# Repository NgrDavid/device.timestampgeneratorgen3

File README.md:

## Harp Timestamp Generator Gen3

This device generates programable timestamps to up to 6 harp devices.

### Key Features ###

* TBA

### Connectivity ###

* TBA

## Interface ##

The interface with the Harp Output Expander can be done through [Bonsai](https://bonsai-rx.org/).

## Licensing ##

Each subdirectory will contain a license or, possibly, a set of licenses if it involves both hardware and software.

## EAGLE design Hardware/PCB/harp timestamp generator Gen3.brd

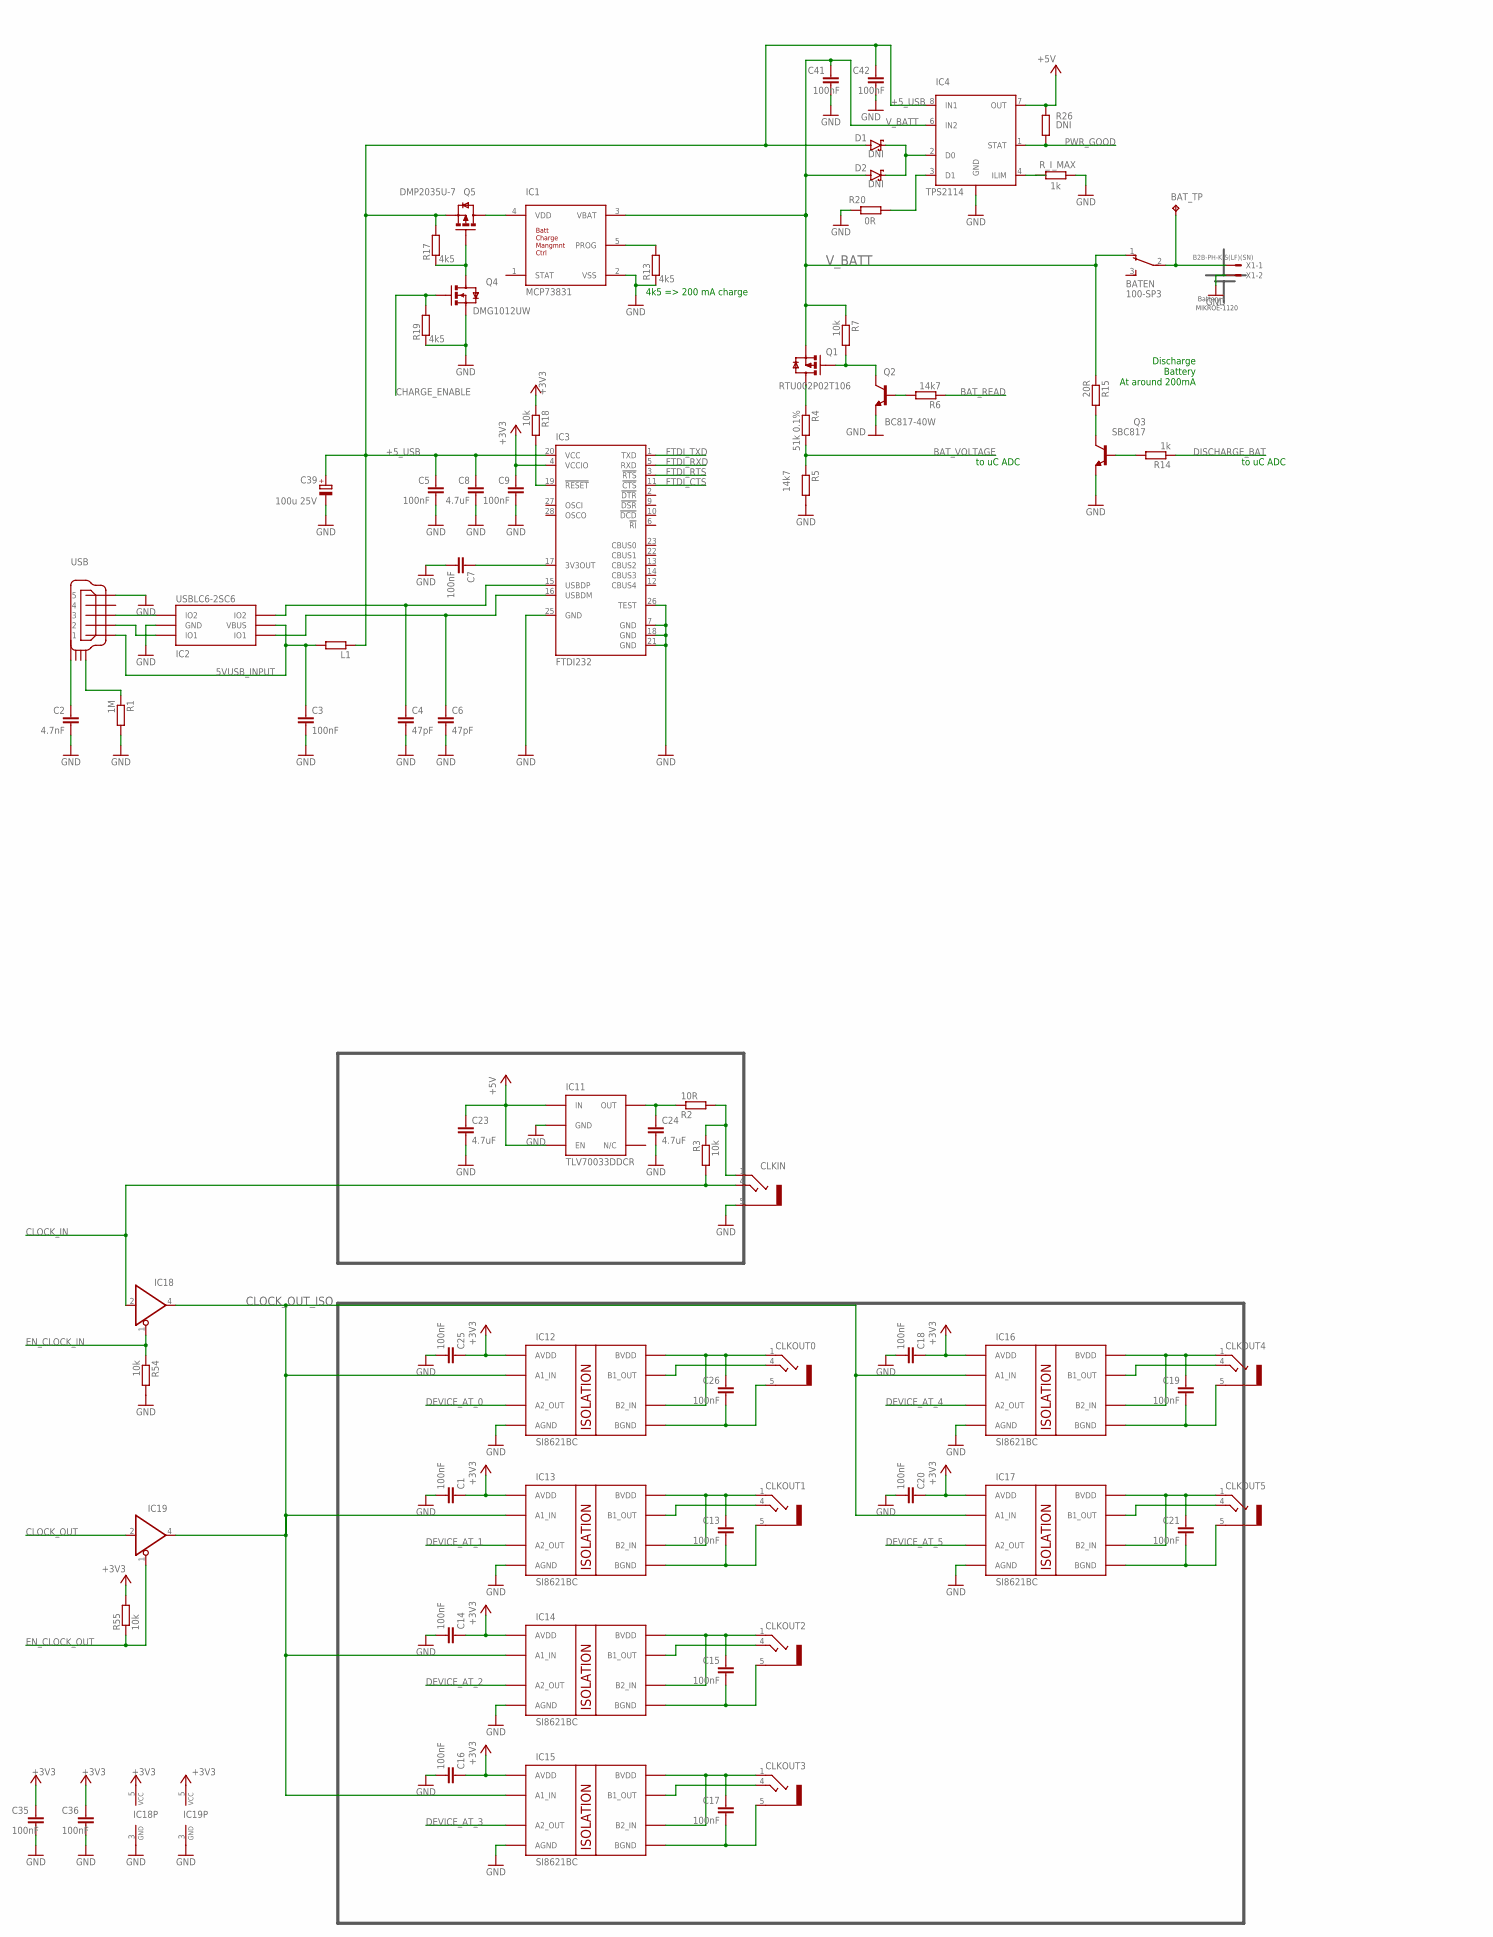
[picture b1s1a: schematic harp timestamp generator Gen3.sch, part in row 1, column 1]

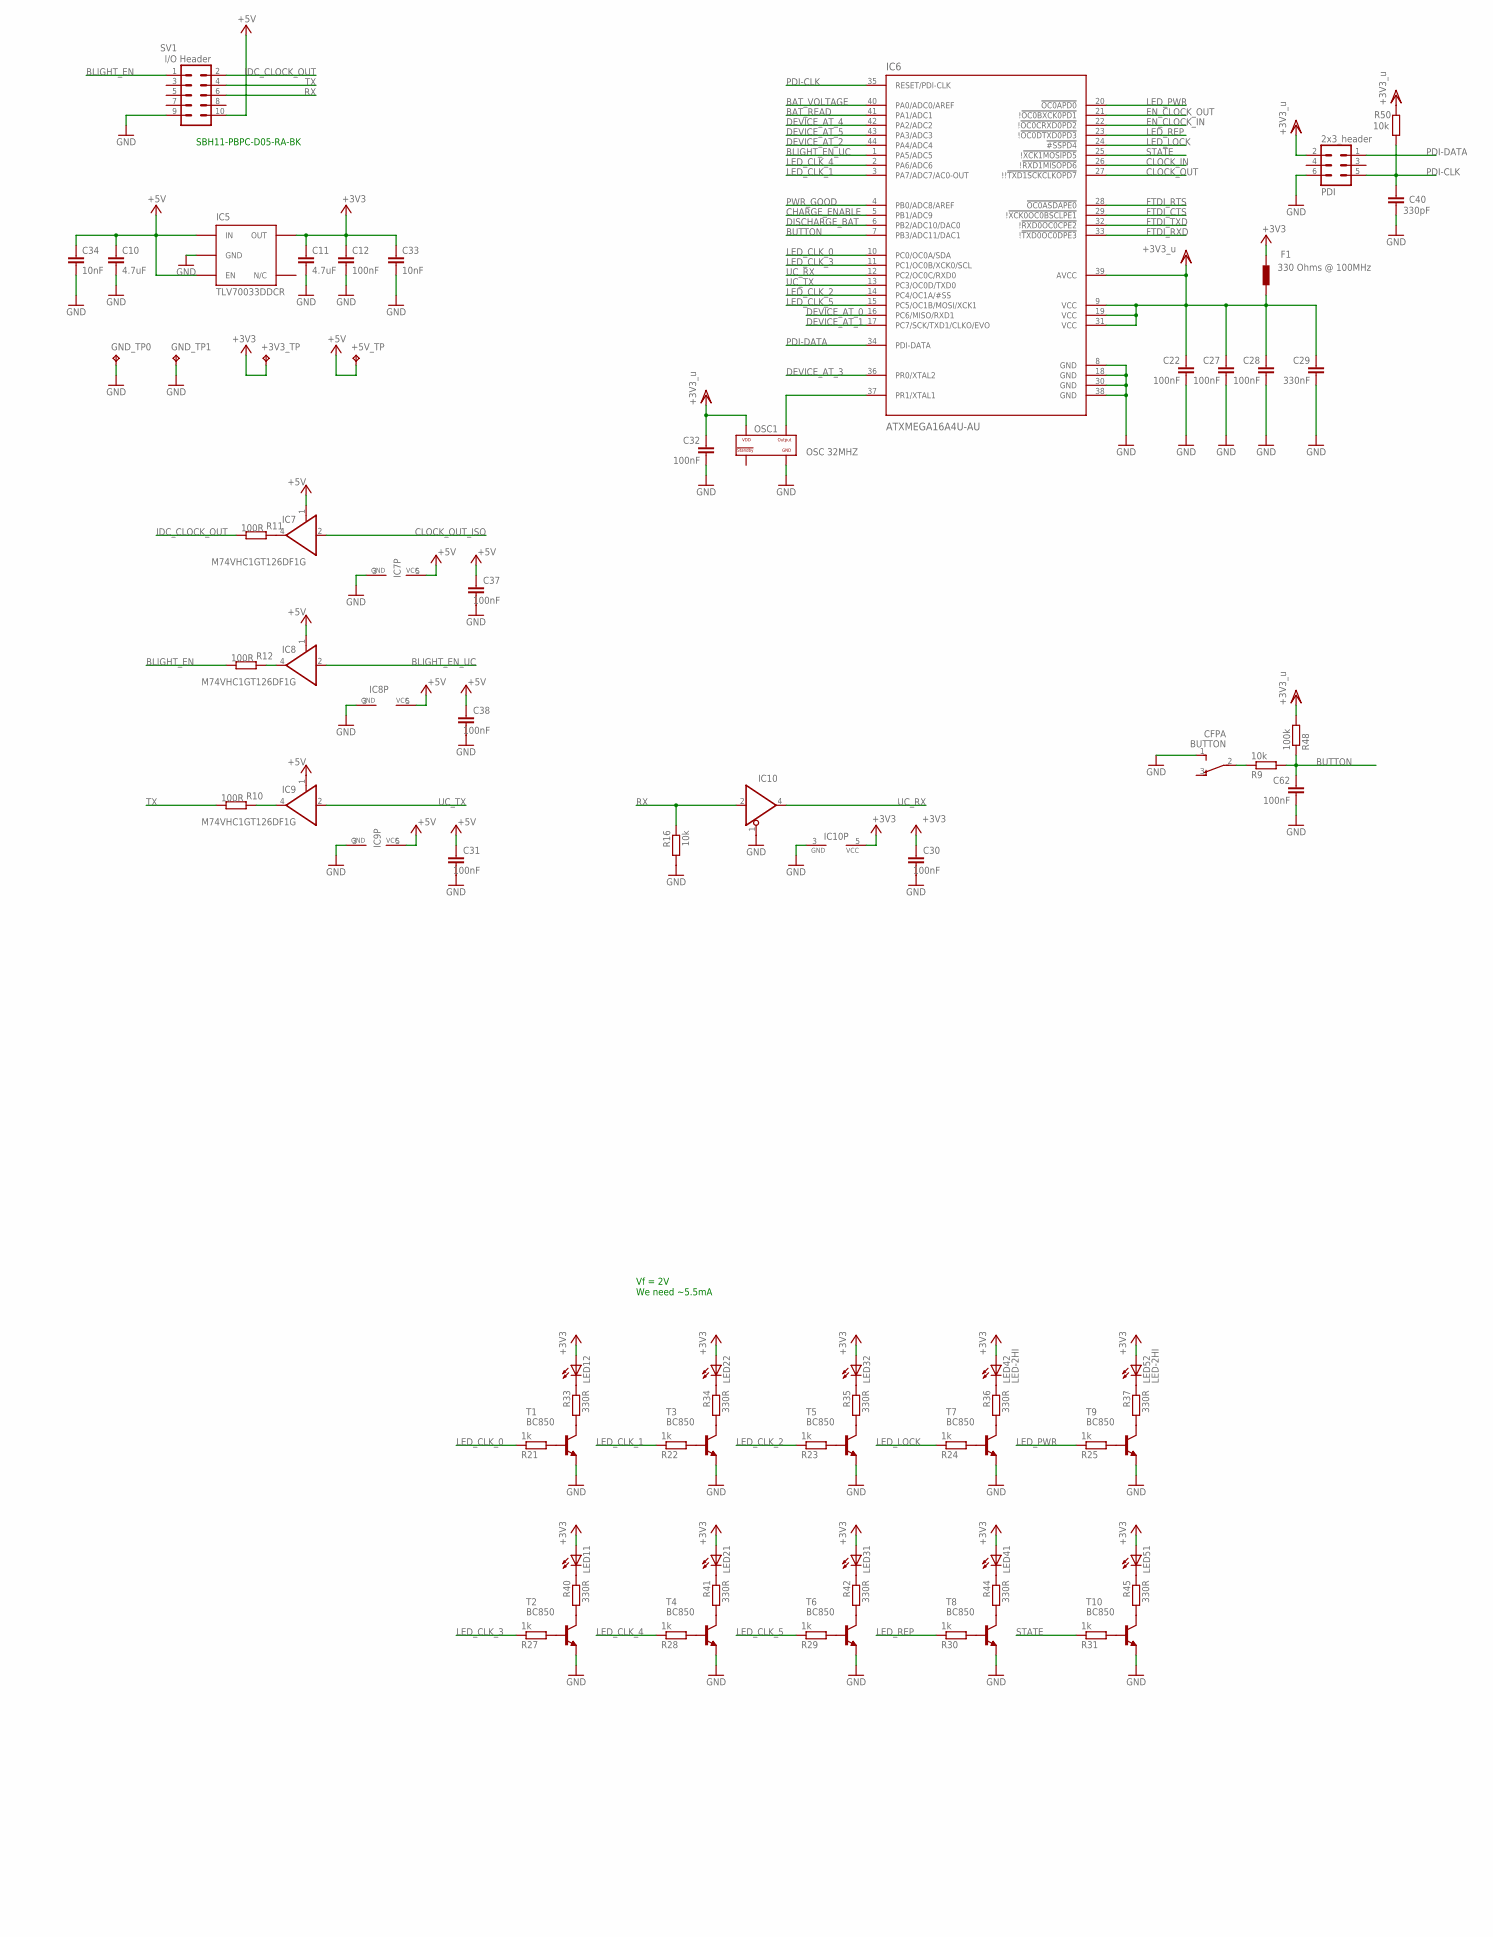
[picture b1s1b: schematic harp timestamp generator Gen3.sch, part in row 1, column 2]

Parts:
+3V3_TP, +5V_TP: TPPAD1-13; P1-13; MPN n.a.
BATEN: 100-SP3; 2M1-SP1-T2-B4-M6RE; MPN 7101MD9ABE; DIGIKEY_PN CKN1045-ND Mouser: 611-7101-051
BAT_TP: TPPAD1-13; P1-13; MPN n.a.
BUTTON: CFPA; MPN CFPA-1FB4-A2T; DIGIKEY_PN 563-1246-1-ND
C1, C3, C5, C7, C9, C12, C13, C14, C15, C16, C17, C18, C19, C20, C21, C22, C25, C26, C27, C28, C30, C31, C32, C35, C36, C37, C38, C41, C42, C62: 100nF; C0402; MPN CGA2B3X7R1H104K050BB; DIGIKEY_PN 445-6899-2-ND
C2: 4.7nF; C0402; MPN UMK105B7472KV-F; DIGIKEY_PN 587-2237-1-ND
C4, C6: 47pF; C0402; MPN 04025A470JAT2A; DIGIKEY_PN 478-1078-1-ND
C8, C10, C11, C23, C24: 4.7uF; C0603; MPN EMK107ABJ475KA-T; DIGIKEY_PN 587-2786-1-ND
C29: 330nF; C0402; MPN GRM155R61A334KE15D; DIGIKEY_PN 490-3263-1-ND
C33, C34: 10nF; C0402; MPN CL05B103KB5NNNC; DIGIKEY_PN 1276-1028-1-ND
C39: 100u 25V; TT2D6; MPN EEUFM1E101B; DIGIKEY_PN P19702CT-ND
C40: 330pF; C0402; MPN C0402C331JAGAC7867; DIGIKEY_PN 399-11875-1-ND
CLKIN: CLCK_JACK; 35RASMT2BHNTRX; MPN 35RASMT2BHNTRX; DIGIKEY_PN SC1489-1-ND
CLKOUT0, CLKOUT1, CLKOUT2, CLKOUT3, CLKOUT4, CLKOUT5: CLCK_JACK; 35RASMT2BHNTRX; MPN 35RASMT2BHNTRX; DIGIKEY_PN SC1489-1-ND
D1, D2: DNI; SOD3715X135
F1: 330 Ohms @ 100MHz; R0603; MPN BLM18SG331TN1D; DIGIKEY_PN 490-3997-1-ND
GND_TP0, GND_TP1: TPPAD1-13; P1-13; MPN n.a.
IC1: MCP73831; TSOT23-5; DIGIKEY_PN MCP73831T-2ATI/OTCT-ND
IC2: USBLC6-2SC6; SOT23-6L; MPN USBLC6-2SC6; DIGIKEY_PN 497-5235-1-ND
IC3: FTDI232; SSOP28; MPN FT232RL-REEL; DIGIKEY_PN 768-1007-1-ND
IC4: TPS2114; TSSOP8; MPN TPS2114APWR; DIGIKEY_PN 296-16939-1-ND
IC5, IC11: TLV70033DDCR; TSOT23-5; MPN TLV70033DDCR; DIGIKEY_PN 296-27937-6-ND
IC6: ATXMEGA16A4U-AU; QFP80P1200X1200X120-44N; MPN ATXMEGA16A4U-AU; DIGIKEY_PN ATXMEGA16A4U-AU-ND
IC7, IC8, IC9: M74VHC1GT126DF1G; SC70-5; MPN M74VHC1GT126DF1G; DIGIKEY_PN M74VHC1GT126DF1GOSCT-ND
IC10, IC18, IC19: SN74LVC1G125DBVT; SOT23-5; MPN SN74LVC1G125DBVT; DIGIKEY_PN 296-26595-1-ND
IC12, IC13, IC14, IC15, IC16, IC17: SI8621BC; SOIC8; MPN Si8621BC-B-IS; DIGIKEY_PN 336-2064-5-ND
L1: 40R@100MHz; R0805; MPN MI0805K400R-10; DIGIKEY_PN 240-2389-1-ND
LED1, LED2, LED3, LED4, LED5: LED-2HI; 569-011X-X00_LED_ARRAY; MPN 5690111100F; DIGIKEY_PN 350-1782-ND
OSC1: OSC 32MHZ; OSCILLATOR_3.2X2.5; MPN O 32,0-JT32C-A-K-3,3-LF; DIGIKEY_PN 1908-1044-1-ND
PDI: 2x3_header; MA03-2; MPN 67996-206HLF; DIGIKEY_PN 609-3210-ND
Q1: RTU002P02T106; SOT323; MPN RTU002P02T106; DIGIKEY_PN RTU002P02T106CT-ND
Q2: BC817-40W; SOT323-BEC; MPN BC817-40W,135; DIGIKEY_PN 1727-6185-1-ND
Q3: SBC817; SOT23-BEC; MPN SBC817-40LT1G; DIGIKEY_PN SBC817-40LT1GOSCT-ND
Q4: DMG1012UW; SOT323; MPN DMG1012UW-7; DIGIKEY_PN DMG1012UW-7DICT-ND
Q5: DMP2035U-7; SOT323; DIGIKEY_PN DMP2035U-7DICT-ND
R1: 1M; R0402; MPN CRCW04021M00FKEDC; DIGIKEY_PN 541-3965-1-ND
R2: 10R; R0402; MPN CRCW040210R0FKEDHP; DIGIKEY_PN 541-10.0YCT-ND
R3, R7, R9, R16, R18, R50, R54, R55: 10k; R0402; MPN RMCF0402FT10K0; DIGIKEY_PN RMCF0402FT10K0CT-ND
R4: 51k 0.1%; R0402; MPN ERA-2AEB513X; DIGIKEY_PN P51KDCCT-ND
R5, R6: 14k7; R0402; MPN RT0402BRD0714K7L; DIGIKEY_PN YAG4174CT-ND
R10, R11, R12: 100R; R0603; MPN RT0603DRD07100RL; DIGIKEY_PN 311-100DCT-ND
R13, R17, R19: 4k5; R0402; MPN RT0402BRD074K53L; DIGIKEY_PN YAG1444CT-ND
R14, R21, R22, R23, R24, R25, R27, R28, R29, R30, R31: 1k; R0402; MPN RMCF0402FT1K00; DIGIKEY_PN RMCF0402FT1K00CT-ND
R15: 20R; R2512; MPN RCP2512W25R0GEB; DIGIKEY_PN 541-2662-1-ND
R20: 0R; R0402; MPN RMCF0402ZT0R00; DIGIKEY_PN RMCF0402ZT0R00CT-ND
R26: DNI; R0402; MPN DNI; DIGIKEY_PN DNI
R33, R34, R35, R36, R37, R40, R41, R42, R44, R45: 330R; R0402; MPN RC0402FR-07330RL; DIGIKEY_PN 311-330LRCT-ND
R48: 100k; R0402; MPN ERJ-2RHD1002X; DIGIKEY_PN P15984CT-ND
R_I_MAX: 1k; R0402; MPN RMCF0402FT1K00; DIGIKEY_PN RMCF0402FT1K00CT-ND Mouser ERJ-2RKF1001X
SV1: I/O Header; ML10L; MPN SBH11-PBPC-D05-RA-BK; DIGIKEY_PN S9177-ND
T1, T2, T3, T4, T5, T6, T7, T8, T9, T10: BC850; SOT23; MPN BC850C,215; DIGIKEY_PN 1727-4862-1-ND
USB: mini USB; 240-0002-1; MPN UX60-MB-5S8; DIGIKEY_PN H2960TR-ND
X1: B2B-PH-K-S(LF)(SN); JST-XH-02-PACKAGE-ROUND-PAD; MPN B2B-PH-K-S(LF)(SN); DIGIKEY_PN 455-1704-ND

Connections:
5VUSB_INPUT: C3.1, IC2.P$5 (VBUS), L1.2, USB.P$1 (1)
+3V3: +3V3_TP.TP, C1.1, C9.1, C11.1, C12.1, C14.1, C16.1, C18.1, C20.1, C25.1, C30.1, C33.1, C35.1, C36.1, F1.2, IC3.4 (VCCIO), IC5.5 (OUT), IC10.5 (VCC), IC12.1 (AVDD), IC13.1 (AVDD), IC14.1 (AVDD), IC15.1 (AVDD), IC16.1 (AVDD), IC17.1 (AVDD), IC18.5 (VCC), IC19.5 (VCC), LED1.A1 (A), LED1.A2 (A), LED2.A1 (A), LED2.A2 (A), LED3.A1 (A), LED3.A2 (A), LED4.A1 (A), LED4.A2 (A), LED5.A1 (A), LED5.A2 (A), R18.1, R55.2
+5V: +5V_TP.TP, C10.1, C23.1, C31.1, C34.1, C37.1, C38.1, IC4.7 (OUT), IC5.1 (IN), IC5.3 (EN), IC7.1 (OE), IC7.5 (VCC), IC8.1 (OE), IC8.5 (VCC), IC9.1 (OE), IC9.5 (VCC), IC11.1 (IN), IC11.3 (EN), R26.1, SV1.10
+5_USB: C5.1, C8.1, C39.+, C42.1, D1.2 (A), IC3.20 (VCC), IC4.8 (IN1), L1.1, Q5.1 (S), R17.2
BAT_READ: IC6.41 (PA1/ADC1), R6.1
BAT_VOLTAGE: IC6.40 (PA0/ADC0/AREF), R4.2, R5.1
BLIGHT_EN: R12.1, SV1.1
BLIGHT_EN_UC: IC6.1 (PA5/ADC5), IC8.2 (I)
BUTTON: C62.1, IC6.7 (PB3/ADC11/DAC1), R9.2, R48.1
CHARGE_ENABLE: IC6.5 (PB1/ADC9), Q4.2 (G), R19.2
CLKOUT0: CLKOUT0.4, IC12.7 (B1_OUT)
CLKOUT1: CLKOUT1.4, IC13.7 (B1_OUT)
CLKOUT2: CLKOUT2.4, IC14.7 (B1_OUT)
CLKOUT3: CLKOUT3.4, IC15.7 (B1_OUT)
CLKOUT4: CLKOUT4.4, IC16.7 (B1_OUT)
CLKOUT5: CLKOUT5.4, IC17.7 (B1_OUT)
CLOCK_IN: CLKIN.4, IC6.26 (!!RXD1MISOPD6), IC18.2 (I), R3.2
CLOCK_OUT: IC6.27 (!!!TXD1SCKCLKOPD7), IC19.2 (I)
CLOCK_OUT_ISO: IC7.2 (I), IC12.2 (A1_IN), IC13.2 (A1_IN), IC14.2 (A1_IN), IC15.2 (A1_IN), IC16.2 (A1_IN), IC17.2 (A1_IN), IC18.4 (O), IC19.4 (O)
DEVICE_AT_0: IC6.16 (PC6/MISO/RXD1), IC12.3 (A2_OUT)
DEVICE_AT_1: IC6.17 (PC7/SCK/TXD1/CLKO/EVO), IC13.3 (A2_OUT)
DEVICE_AT_2: IC6.44 (PA4/ADC4), IC14.3 (A2_OUT)
DEVICE_AT_3: IC6.36 (PR0/XTAL2), IC15.3 (A2_OUT)
DEVICE_AT_4: IC6.42 (PA2/ADC2), IC16.3 (A2_OUT)
DEVICE_AT_5: IC6.43 (PA3/ADC3), IC17.3 (A2_OUT)
DISCHARGE_BAT: IC6.6 (PB2/ADC10/DAC0), R14.1
EN_CLOCK_IN: IC6.22 (!!OC0CRXD0PD2), IC18.1 (OE), R54.1
EN_CLOCK_OUT: IC6.21 (!!OC0BXCK0PD1), IC19.1 (OE), R55.1
FTDI_CTS: IC3.11 (!CTS), IC6.29 (!!XCK0OC0BSCLPE1)
FTDI_RTS: IC3.3 (!RTS), IC6.28 (!OC0ASDAPE0)
FTDI_RXD: IC3.5 (RXD), IC6.33 (!!TXD0OC0DPE3)
FTDI_TXD: IC3.1 (TXD), IC6.32 (!!RXD0OC0CPE2)
GND: BUTTON.1 (3), C1.2, C2.2, C3.2, C4.2, C5.2, C6.2, C7.2, C8.2, C9.2, C10.2, C11.2, C12.2, C14.2, C16.2, C18.2, C20.2, C22.2, C23.2, C24.2, C25.2, C27.2, C28.2, C29.2, C30.2, C31.2, C32.2, C33.2, C34.2, C35.2, C36.2, C37.2, C38.2, C39.-, C40.2, C41.2, C42.2, C62.2, CLKIN.5, GND_TP0.TP, GND_TP1.TP, IC1.2 (VSS), IC2.P$2 (GND), IC3.7 (GND), IC3.18 (GND), IC3.21 (GND), IC3.25 (GND), IC3.26 (TEST), IC4.5 (GND), IC5.2 (GND), IC6.8 (GND), IC6.18 (GND), IC6.30 (GND), IC6.38 (GND), IC7.3 (GND), IC8.3 (GND), IC9.3 (GND), IC10.1 (OE), IC10.3 (GND), IC11.2 (GND), IC12.4 (AGND), IC13.4 (AGND), IC14.4 (AGND), IC15.4 (AGND), IC16.4 (AGND), IC17.4 (AGND), IC18.3 (GND), IC19.3 (GND), OSC1.P$2 (GND), PDI.6, Q2.E, Q3.E, Q4.1 (S), R1.2, R5.2, R13.1, R16.2, R19.1, R20.1, R54.2, R_I_MAX.2, SV1.9, T1.2 (E), T2.2 (E), T3.2 (E), T4.2 (E), T5.2 (E), T6.2 (E), T7.2 (E), T8.2 (E), T9.2 (E), T10.2 (E), USB.P$5 (5), X1.2
GND_ISO: C26.2, CLKOUT0.5, IC12.5 (BGND)
GND_ISO1: C13.2, CLKOUT1.5, IC13.5 (BGND)
GND_ISO2: C15.2, CLKOUT2.5, IC14.5 (BGND)
GND_ISO3: C17.2, CLKOUT3.5, IC15.5 (BGND)
GND_ISO4: C19.2, CLKOUT4.5, IC16.5 (BGND)
GND_ISO5: C21.2, CLKOUT5.5, IC17.5 (BGND)
IDC_CLOCK_OUT: R11.1, SV1.2
LED_CLK_0: IC6.10 (PC0/OC0A/SDA), R21.1
LED_CLK_1: IC6.3 (PA7/ADC7/AC0-OUT), R22.1
LED_CLK_2: IC6.14 (PC4/OC1A/#SS), R23.1
LED_CLK_3: IC6.11 (PC1/OC0B/XCK0/SCL), R27.1
LED_CLK_4: IC6.2 (PA6/ADC6), R28.1
LED_CLK_5: IC6.15 (PC5/OC1B/MOSI/XCK1), R29.1
LED_LOCK: IC6.24 (!#SSPD4), R24.1
LED_PWR: IC6.20 (!OC0APD0), R25.1
LED_REP: IC6.23 (!!OC0DTXD0PD3), R30.1
unnamed: R24.2, T7.1 (B)
unnamed: Q4.3 (D), Q5.2 (G), R17.1
unnamed: IC8.4 (O), R12.2
unnamed: IC9.4 (O), R10.2
unnamed: C26.1, CLKOUT0.1, IC12.6 (B2_IN), IC12.8 (BVDD)
unnamed: C13.1, CLKOUT1.1, IC13.6 (B2_IN), IC13.8 (BVDD)
unnamed: R36.2, T7.3 (C)
unnamed: IC7.4 (O), R11.2
unnamed: IC1.4 (VDD), Q5.3 (D)
unnamed: C15.1, CLKOUT2.1, IC14.6 (B2_IN), IC14.8 (BVDD)
unnamed: R22.2, T3.1 (B)
unnamed: IC1.5 (PROG), R13.2
unnamed: R21.2, T1.1 (B)
unnamed: LED3.C1 (C), R42.1
unnamed: R33.2, T1.3 (C)
unnamed: R27.2, T2.1 (B)
unnamed: R34.2, T3.3 (C)
unnamed: R40.2, T2.3 (C)
unnamed: LED3.C2 (C), R35.1
unnamed: R28.2, T4.1 (B)
unnamed: R41.2, T4.3 (C)
unnamed: R23.2, T5.1 (B)
unnamed: R35.2, T5.3 (C)
unnamed: R29.2, T6.1 (B)
unnamed: R42.2, T6.3 (C)
unnamed: LED1.C2 (C), R33.1
unnamed: LED2.C2 (C), R34.1
unnamed: LED1.C1 (C), R40.1
unnamed: LED2.C1 (C), R41.1
unnamed: R30.2, T8.1 (B)
unnamed: Q3.B, R14.2
unnamed: Q3.C, R15.2
unnamed: C17.1, CLKOUT3.1, IC15.6 (B2_IN), IC15.8 (BVDD)
unnamed: C7.1, IC3.17 (3V3OUT)
unnamed: IC2.P$1 (IO1), USB.P$2 (2)
unnamed: CLKIN.1, R2.2, R3.1
unnamed: C24.1, IC11.5 (OUT), R2.1
unnamed: BUTTON.2, R9.1
unnamed: C19.1, CLKOUT4.1, IC16.6 (B2_IN), IC16.8 (BVDD)
unnamed: R44.2, T8.3 (C)
unnamed: C21.1, CLKOUT5.1, IC17.6 (B2_IN), IC17.8 (BVDD)
unnamed: IC2.P$3 (IO2), USB.P$3 (3)
unnamed: R25.2, T9.1 (B)
unnamed: R37.2, T9.3 (C)
unnamed: R31.2, T10.1 (B)
unnamed: C2.1, USB.SHIELD_4
unnamed: R45.2, T10.3 (C)
unnamed: R1.1, USB.SHIELD_1
unnamed: LED5.C1 (C), R45.1
unnamed: LED5.C2 (C), R37.1
unnamed: LED4.C2 (C), R36.1
unnamed: LED4.C1 (C), R44.1
unnamed: BATEN.2, BAT_TP.TP, X1.1
unnamed: Q1.3 (D), R4.1
unnamed: IC4.4 (ILIM), R_I_MAX.1
unnamed: Q1.2 (G), Q2.C, R7.2
unnamed: Q2.B, R6.2
unnamed: D1.1 (C), D2.1 (C), IC4.2 (D0)
unnamed: IC4.3 (D1), R20.2
unnamed: IC3.19 (!RESET), R18.2
OSC1: IC6.37 (PR1/XTAL1), OSC1.P$3 (OUTPUT)
PDI-CLK: C40.1, IC6.35 (RESET/PDI-CLK), PDI.5, R50.1
PDI-DATA: IC6.34 (PDI-DATA), PDI.1
PWR_GOOD: IC4.1 (STAT), IC6.4 (PB0/ADC8/AREF), R26.2
RX: IC10.2 (I), R16.1, SV1.6
STATE: IC6.25 (!!XCK1MOSIPD5), R31.1
TX: R10.1, SV1.4
UC_RX: IC6.12 (PC2/OC0C/RXD0), IC10.4 (O)
UC_TX: IC6.13 (PC3/OC0D/TXD0), IC9.2 (I)
USBDM: C6.1, IC2.P$6 (IO1), IC3.16 (USBDM)
USBDP: C4.1, IC2.P$4 (IO2), IC3.15 (USBDP)
VDD: C22.1, C27.1, C28.1, C29.1, C32.1, F1.1, IC6.9 (VCC), IC6.19 (VCC), IC6.31 (VCC), IC6.39 (AVCC), OSC1.P$4 (VDD), PDI.2, R48.2, R50.2
V_BATT: BATEN.1, C41.1, D2.2 (A), IC1.3 (VBAT), IC4.6 (IN2), Q1.1 (S), R7.1, R15.1

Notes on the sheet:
Vf = 2V We need ~5.5mA
SBH11-PBPC-D05-RA-BK
4k5 => 200 mA charge
Battery
to uC ADC
MIKROE-1120
Discharge Battery At around 200mA

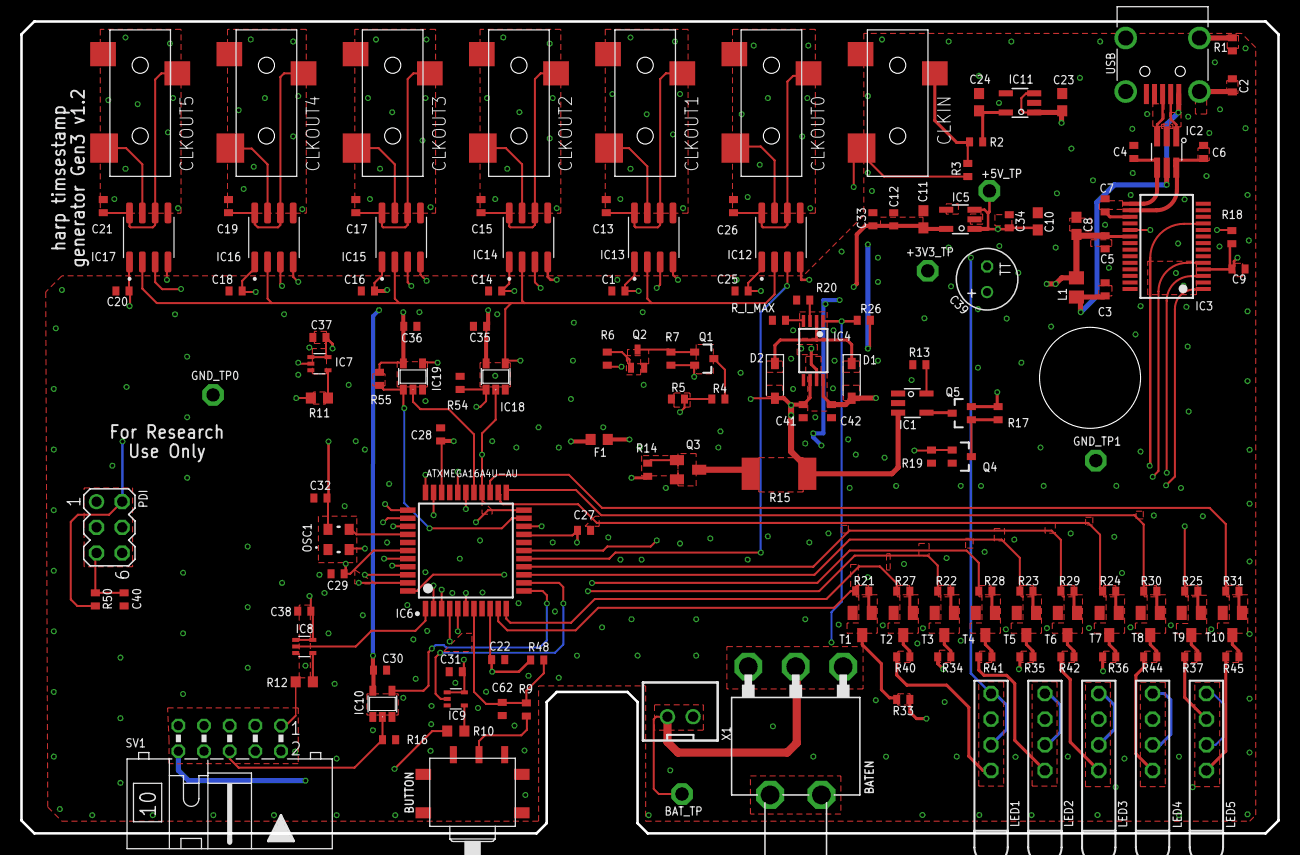
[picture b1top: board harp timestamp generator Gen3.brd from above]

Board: 4 copper layers, 124.5 x 80.4 mm, 150 parts (0 on the bottom side), 122 nets.

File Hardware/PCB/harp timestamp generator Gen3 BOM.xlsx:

Qty | Value | Package | Parts | MPN | Type
ASSEMBLY HOUSE
1 | CFPA | CFPA | BUTTON | CFPA-1FB4-A2T | SMD
30 | 100nF | C0402 | C1, C3, C5, C7, C9, C12, C13, C14, C15, C16, C17, C18, C19, C20, C21, C22, C25,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 | CGA2B3X7R1H104K050BB | SMD
5 | 4.7uF | C0603 | C8, C10, C11, C23, C24 | C1608X6S1C475K080AC | SMD
1 | 4.7nF | C0402 | C2 | 885012205084 | SMD
1 | 330nF | C0402 | C29 | GRM155R61A334KE15D | SMD
2 | 10nF | C0402 | C33, C34 | GCM155R71E103KA37D | SMD
2 | 47pF | C0402 | C4, C6 | 04025A470JAT2A | SMD
1 | 100u 25V | TT2D6 | C39 | EEU-FM1E101B | TH
1 | 330pF | C0402 | C40 | C0402C331J5GAC7867 | SMD
7 | CLCK_JACK | 35RASMT2BHNTRX | CLKIN, CLKOUT0, CLKOUT1, CLKOUT2, CLKOUT3, CLKOUT4, CLKOUT5 | 35RASMT2BHNTRX | SMD
1 | 330 Ohms @ 100MHz | R0603 | F1 | BLM18SG331TN1D | SMD
2 | DNI | DNI | D1, D2 | DNI | DNI
1 | MCP73831T-2ATI/OT | TSOT23-5 | IC1 | MCP73831T-2ATI/OT | SMD
3 | SN74LVC1G125DBVT | SOT23-5 | IC10, IC18, IC19 | SN74LVC1G125DBVT | SMD
6 | SI8621BC-B-IS | SOIC8 | IC12, IC13, IC14, IC15, IC16, IC17 | SI8621BC-B-ISR | SMD | Replacements: SI8621BB-B-IS
1 | USBLC6-2SC6 | SOT23-6L | IC2 | USBLC6-2SC6 | SMD
1 | FT232RL | SSOP28 | IC3 | FT232RL-REEL | SMD
1 | TPS2114 | TSSOP8 | IC4 | TPS2114APWR | SMD
2 | TLV70033DDCR | TSOT23-5 | IC5, IC11 | LP5951MFX-3.3/NOPB | SMD
1 | ATXMEGA16A4U-AU | QFP80P1200X1200X120-44N | IC6 | ATXMEGA16A4U-A | SMD
3 | M74VHC1GT126DF1G | SC70-5 | IC7, IC8, IC9 | M74VHC1GT126DF1G | SMD
1 | 40R@100MHz | R0805 | L1 | MI0805K400R-10 | SMD
5 | 569-0112-100 | 569-011X-X00_LED_ARRAY | LED1, LED2, LED3, LED4, LED5 | 569-0111-100F | TH
1 | OSCILLATOR | OSCILLATOR_3.2X2.5 | OSC1 | O 32,0-JT32C-A-K-3,3-LF | SMD
1 | 2x3_header | MA03-2 | PDI | 67996-206HLF | TH
1 | RTU002P02T106 | SOT323 | Q1 | RTU002P02T106 | SMD
1 | BC817-40W | SOT323-BEC | Q2 | BC817-40W,135 | SMD
1 | BC817-40LT1SMD | SOT23-BEC | Q3 | SBC817-40LT1G | SMD
1 | DMG1012UW | SOT323 | Q4 | DMG1012UW-7 | SMD
1 | DMP2035U-7 | SOT323 | Q5 | DMP2035U-7 | SMD
1 | 1M | R0402 | R1 | CRCW04021M00FKED | SMD
3 | 100R | R0603 | R10, R11, R12 | CRCW0603100RFKEAHP | SMD
3 | 4k5 | R0402 | R13, R17, R19 | RT0402BRD074K53L | SMD
1 | 20R | R2512 | R15 | CRM2512-FX-20R0ELF | SMD
1 | 10R | R0402 | R2 | ERJ-PA2J100X | SMD
1 | 0R | R0402 | R20 | RC0402JR-070RL | SMD
1 | DNI | R0402 | R26 | DNI | DNI
12 | 1k | R0402 | R14, R21, R22, R23, R24, R25, R27, R28, R29, R30, R31, R_I_MAX | CRCW04021K00FKED | SMD
8 | 10k | R0402 | R3, R7, R9, R16, R18, R50, R54, R55 | CRCW040210K0FKED | SMD
10 | 330R | R0402 | R33, R34, R35, R36, R37, R40, R41, R42, R44, R45 | RC0402FR-07330RL | SMD
1 | 51k 0.1% | R0402 | R4 | ERA-2AEB513X | SMD
2 | 14k7 0.1% | R0402 | R5, R6 | RT0402BRD0714K7L | SMD
1 | 100k | R0402 | R48 | ERJ-2RKF1003X | SMD
1 | I/O Header | ML10L | SV1 | SBH11-PBPC-D05-RA-BK | TH
10 | BC850 | SOT23 | T1, T2, T3, T4, T5, T6, T7, T8, T9, T10 | BC850C,215 | SMD
1 | mini USB | 240-0002-1 | USB | UX60-MB-5S8 | SMD
1 | Switch SPDT | 7101MD9ABE | BATEN | 7101MD9ABE | TH
1 | B2B-PH-K-S(LF)(SN) | JST-XH-02-PACKAGE-ROUND-PAD | X1 | B2B-XH-A(LF)(SN) | TH
POST-PRODUCTION
1 |  |  | Front Panel PCB | PCBWAY
1 |  |  | Rear Panel PCB | PCBWAY
1 |  |  | Enclosure | B5-080BK
1 |  |  | Battery lithium Polymer 2 Ah | MIKROE-1120 | -
4 |  |  | Bumper Cylindrical Dome 9.53mm | SJ-5306-CLEAR-3000/CASE
ACCESSORIES
3 |  |  | 3.5mm stereo jack cable 0.3 m, Black | P312-001 | -
4 |  |  | 3.5mm stereo jack cable 1.2 m, Black | AV13646
1 |  |  | 0.9 left angle USB cable | USB2HABM3RA
NOTES
 |  |  |  | Number of unique parts | 48
 |  |  |  | Number of SMD unique parts | 42
 |  |  |  | Number of SMD parts | 135
 |  |  |  | Number of TH unique parts | 6
 |  |  |  | Number of TH parts | 10

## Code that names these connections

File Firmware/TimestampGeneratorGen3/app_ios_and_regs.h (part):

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// DEVICE_AT_1            Description: Device is connected to CLKOUT1
// DEVICE_AT_3            Description: Device is connected to CLKOUT3

#define read_DEVICE_AT_4 read_io(PORTA, 2)      // DEVICE_AT_4
#define read_DEVICE_AT_5 read_io(PORTA, 3)      // DEVICE_AT_5
#define read_DEVICE_AT_2 read_io(PORTA, 4)      // DEVICE_AT_2
#define read_POWER_GOOD read_io(PORTB, 0)       // POWER_GOOD
#define read_BUTTON read_io(PORTB, 3)           // BUTTON
#define read_DEVICE_AT_0 read_io(PORTC, 6)      // DEVICE_AT_0
#define read_DEVICE_AT_1 read_io(PORTC, 7)      // DEVICE_AT_1
#define read_DEVICE_AT_3 read_io(PORTR, 0)      // DEVICE_AT_3

/************************************************************************/
/* Definition of output pins                                            */
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
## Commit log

2021-04-25 Added first firmware files.
2021-04-25 Added an extra 100uF capacitor to +5_USB.
2021-04-25 Added proper filtering to RESET line.
2021-04-28 Corrected the discharge circuit.
2021-05-03 Added replacements.
2021-05-04 Decreased discharge current by ~60 mA to ~175 mA in average.
2021-05-05 Added ability to initiate battery cycle using the external button.
2022-03-30 Removed LOCK from configuration.
2022-03-30 Enhanced shutdown control and visualizers.
2022-03-30 Removed POWER_GOOD and wake up from buttons' interrupts.
2022-04-02 Updated code to harp core 1.10
2022-05-04 Changed battery connection to a new location and added an ON/OFF button.
2022-05-04 Updated BOM and added front and rear panels.
2022-05-04 Updated Bonsai tests workflow and remapped button interrupt.
2022-05-23 Updated front panel to reflect the right device version.
2022-09-22 Added device's photos.
2022-09-22 Corrected filenames.
2022-10-05 Added a new power switcher.
2022-10-05 Updated copyright dates.
2022-10-05 Corrected bad battery gauge reader.
    When unplugging and plugging the battery on the fly, the reset of the state machine was not working correctly.
2022-10-05 Released first firmware version.
2022-11-17 Minor changes.
2023-03-28 Add resized device shots and update license
2023-03-28 Refactor repository structure
2023-03-28 Add prototype device schema and interface
2023-03-29 Generate symbols package
2023-03-29 Add missing bitmask and group masks
2023-04-03 Corrected files for porduction.
2023-05-09 Replaced Q5 with a correct size component.
2023-05-18 Fixed the stop command to charge/discharge of the battery
2023-05-18 Make paths relative
2023-05-18 Raise firmware version to 1.1
    Also removed the previous Release folder.
    The releases are now available in GitHub releases.
2023-07-31 Update interface to use new generators
2023-08-03 Add missing package metadata for stable release
2023-08-10 Add gitignore to Firmware and Hardware
2023-08-10 Clean repository root
2023-08-10 Updated dates.
2023-08-10 Updated firmware version.
2023-08-10 Replaced harp core 1.10 with 1.13.
2023-08-14 Update PCB image asset
2023-08-14 Re-format temporary readme page
2024-04-03 Fix broken image link
2024-04-03 Fix title heading
2024-04-29 Created new registers.
2024-04-29 Implemented the functionality.
2024-05-22 Added maskType to register TimerFrequency.
2024-05-22 Increased hardware target to v1,2.
2024-05-22 Improve clarity of new registers
2024-05-30 Fixed #7
2024-05-30 Increased hardware version.
2024-05-30 Clean up device.yml
2024-05-30 Regenerate interface
2024-06-07 Remove 0x00 default flag
2024-06-12 Bump interface version
2024-11-09 Fix schema source
2024-11-09 Fix missing property name
2024-11-09 Update generators and regenerate interface
2024-11-09 Update package metadata to embed device metadata
2024-11-10 Favor harp-tech as source of device schema
2025-05-16 Create basic CI/CD for interface package
